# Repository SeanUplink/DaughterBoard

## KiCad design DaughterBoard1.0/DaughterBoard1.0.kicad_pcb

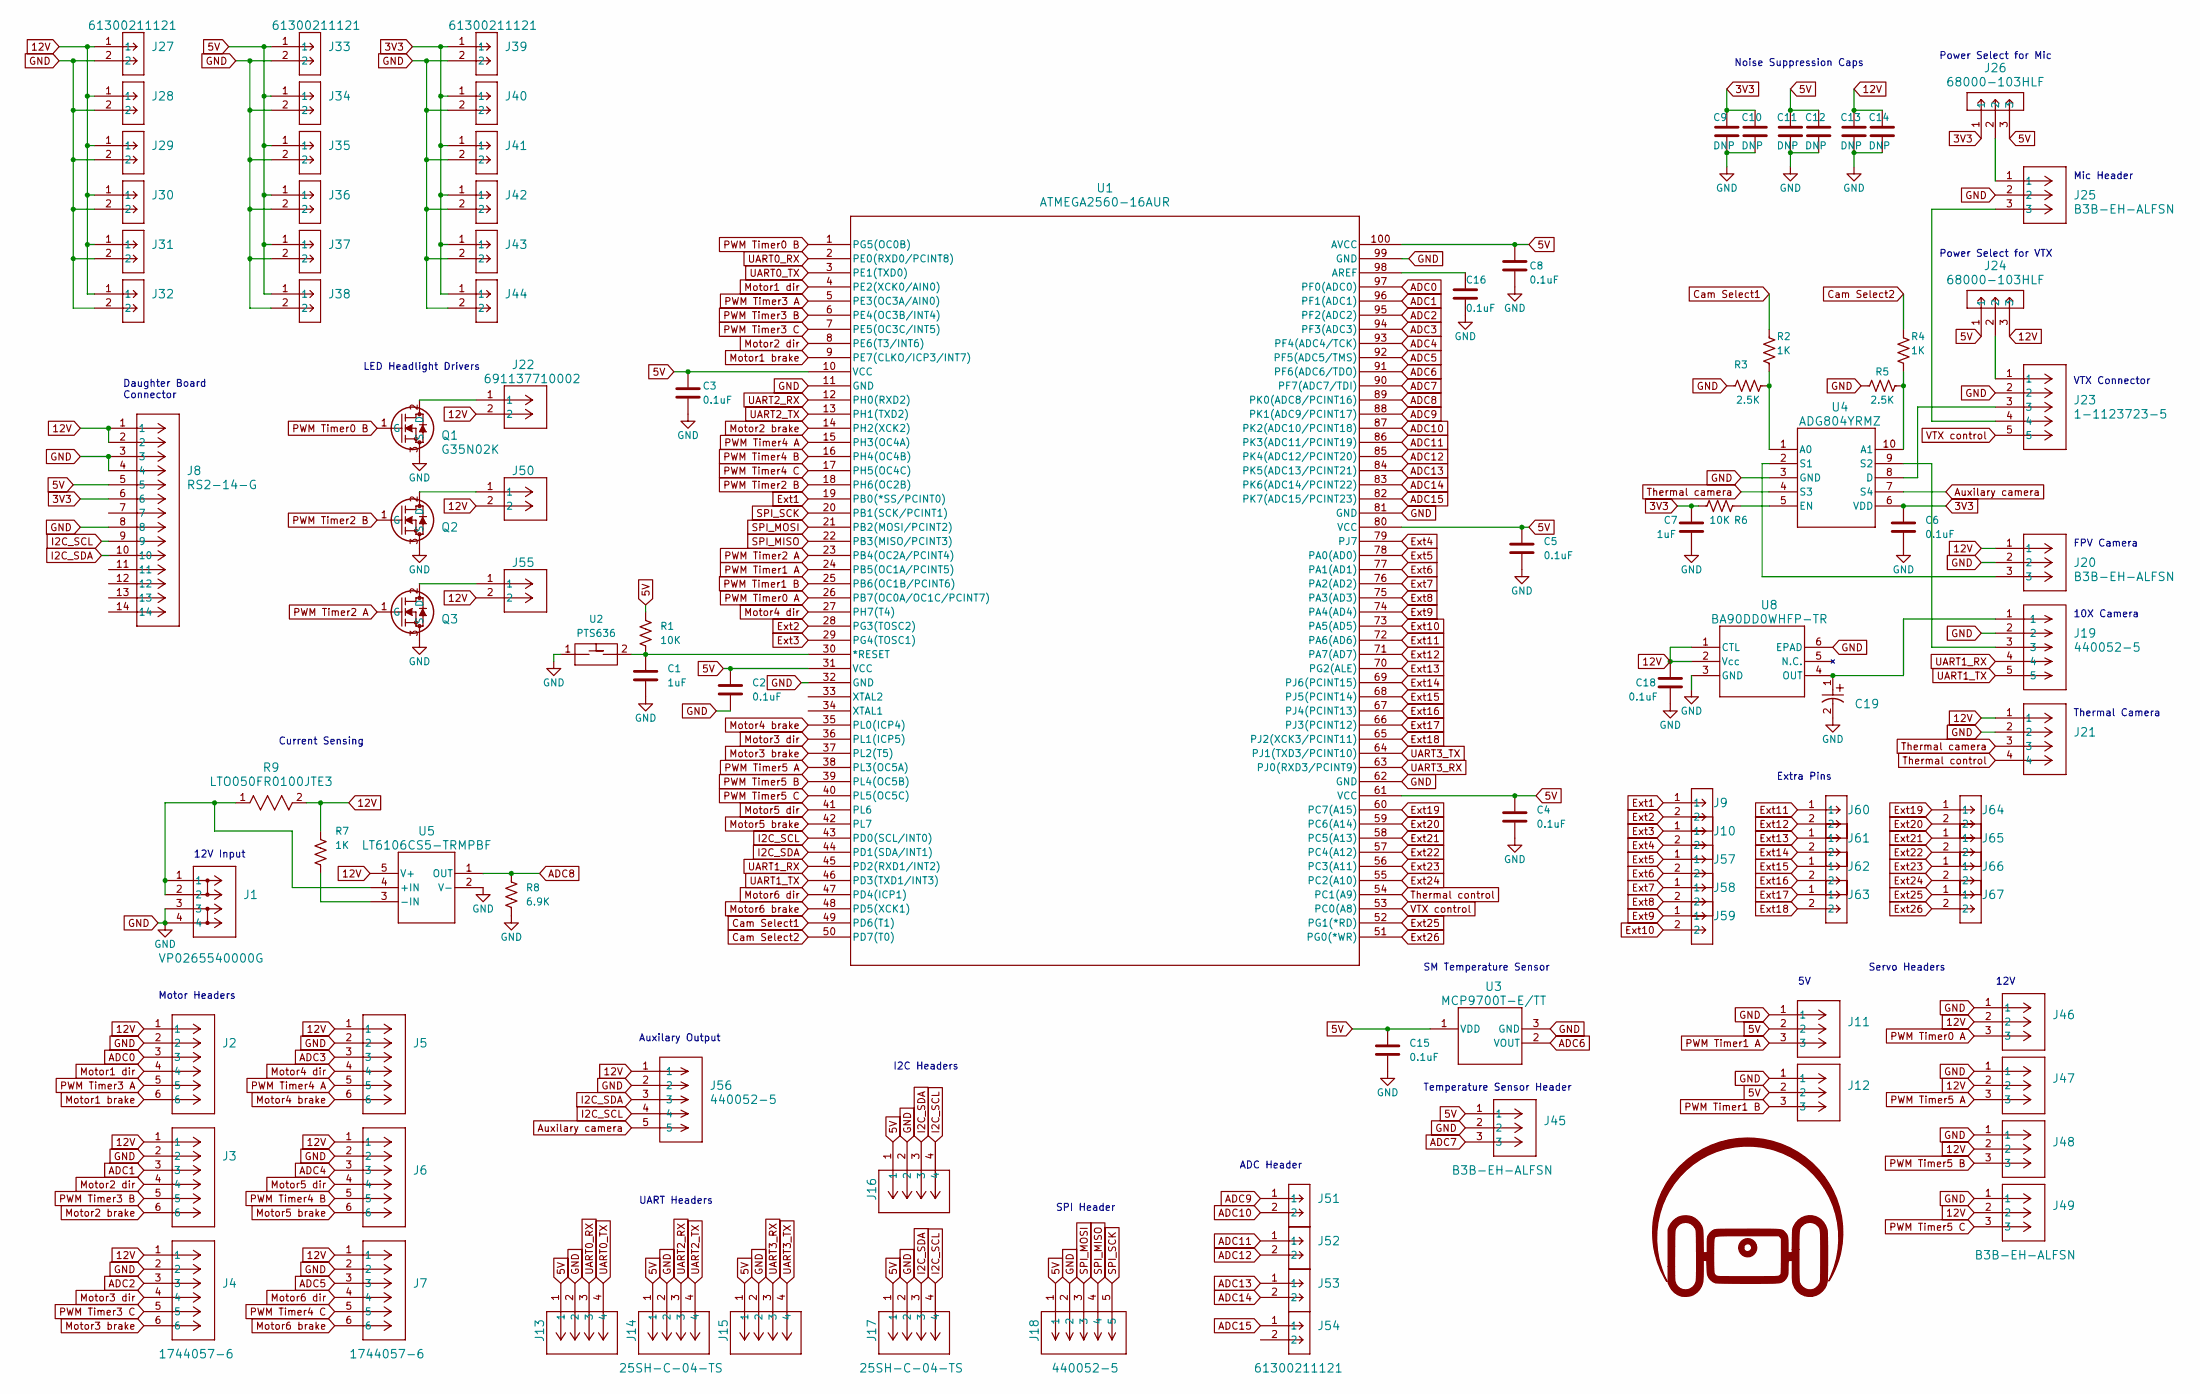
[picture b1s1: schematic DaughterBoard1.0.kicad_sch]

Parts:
C1, C7: 1uF; C_0603_1608Metric
C2, C3, C4, C5, C6, C8, C15, C16: 0.1uF; C_0603_1608Metric
C9, C10, C11, C12, C13, C14: DNP; C_0603_1608Metric
C18: 0.1uF; C_0805_2012Metric_Pad1.18x1.45mm_HandSolder
C19: TAJC226M016RNJ; TAJC_AVX
G1: LOGO; logo
J1: VP0265540000G; CONN_VP0265x4xxxxG_AMP
J2, J3, J4, J5, J6, J7: 1744057-6; conn6_1744057-6_TEC
J8: RS2-14-G; CONN_RS2-14-G_ADM
J9, J10, J27, J28, J29, J30, J31, J32, J33, J34, J35, J36, J37, J38, J39, J40, J41, J42, J43, J44, J51, J52, J53, J54, J57, J58, J59, J60, J61, J62, J63, J64, J65, J66, J67: 61300211121; CONN_61300211121_WRE
J11, J12, J20, J25, J45, J46, J47, J48, J49: B3B-EH-ALFSN; CONN3_B3B-EH-ALFSN_JST
J13, J14, J15, J16, J17, J21: 25SH-C-04-TS; CONN_B4B-EH-A_JST
J18: 440052-5; TE_440052-5; PARTREV R
J19, J56: 440052-5; conn5_1-1123723-5_TEC; PARTREV R
J22, J50, J55: 691137710002; CONN2_710002_WRE
J23: 1-1123723-5; conn5_1-1123723-5_TEC
J24, J26: 68000-103HLF; CONN_68000-103HLF_AMP
Q1, Q2, Q3: G35N02K; QNMOS1G2D3S_TO252DPAK_DIO
R1, R6: 10K; R_0603_1608Metric
R2, R4, R7: 1K; R_0603_1608Metric
R3, R5: 2.5K; R_0603_1608Metric
R8: 6.9K; R_0603_1608Metric
R9: LTO050FR0100JTE3; TO220_LTO_VIS
U1: ATMEGA2560-16AUR; TQFP100_100A_ATM
U2: PTS636
U3: MCP9700T-E/TT; SOT-23_MC_MCH
U4: ADG804YRMZ; RM_10_ADI
U5: LT6106CS5-TRMPBF; TSOT-23-5_S5_ADI
U8: BA90DD0WHFP-TR; HRP5_ROM

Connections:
3V3: C6.1, C7.1, C9.1, C10.1, J8.6, J26.1, J39.1, J40.1, J41.1, J42.1, J43.1, J44.1, R6.1, U4.6 (VDD)
5V: C2.1, C3.1, C4.1, C5.1, C8.1, C11.1, C12.1, C15.1, J8.5, J11.2, J12.2, J13.1, J14.1, J15.1, J16.1, J17.1, J18.1, J24.1, J26.3, J33.1, J34.1, J35.1, J36.1, J37.1, J38.1, J45.1, R1.1, U1.10 (VCC), U1.31 (VCC), U1.61 (VCC), U1.80 (VCC), U1.100 (AVCC), U3.1 (VDD)
12V: C13.1, C14.1, C18.1, J2.1, J3.1, J4.1, J5.1, J6.1, J7.1, J8.1, J8.2, J20.1, J21.1, J22.2, J24.3, J27.1, J28.1, J29.1, J30.1, J31.1, J32.1, J46.2, J47.2, J48.2, J49.2, J50.2, J55.2, J56.1, R7.1, R9.2, U5.5 (V+), U8.1 (CTL), U8.2 (Vcc)
ADC0: J2.3, U1.97 (PF0(ADC0))
ADC1: J3.3, U1.96 (PF1(ADC1))
ADC2: J4.3, U1.95 (PF2(ADC2))
ADC3: J5.3, U1.94 (PF3(ADC3))
ADC4: J6.3, U1.93 (PF4(ADC4/TCK))
ADC5: J7.3, U1.92 (PF5(ADC5/TMS))
ADC6: U1.91 (PF6(ADC6/TDO)), U3.2 (VOUT)
ADC7: J45.3, U1.90 (PF7(ADC7/TDI))
ADC8: R8.1, U1.89 (PK0(ADC8/PCINT16)), U5.1 (OUT)
ADC9: J51.1, U1.88 (PK1(ADC9/PCINT17))
ADC10: J51.2, U1.87 (PK2(ADC10/PCINT18))
ADC11: J52.1, U1.86 (PK3(ADC11/PCINT19))
ADC12: J52.2, U1.85 (PK4(ADC12/PCINT20))
ADC13: J53.1, U1.84 (PK5(ADC13/PCINT21))
ADC14: J53.2, U1.83 (PK6(ADC14/PCINT22))
ADC15: J54.1, U1.82 (PK7(ADC15/PCINT23))
Auxilary camera: J56.5, U4.7 (S4)
Cam Select1: R2.1, U1.49 (PD6(T1))
Cam Select2: R4.1, U1.50 (PD7(T0))
Ext1: J9.1, U1.19 (PB0(*SS/PCINT0))
Ext2: J9.2, U1.28 (PG3(TOSC2))
Ext3: J10.1, U1.29 (PG4(TOSC1))
Ext4: J10.2, U1.79 (PJ7)
Ext5: J57.1, U1.78 (PA0(AD0))
Ext6: J57.2, U1.77 (PA1(AD1))
Ext7: J58.1, U1.76 (PA2(AD2))
Ext8: J58.2, U1.75 (PA3(AD3))
Ext9: J59.1, U1.74 (PA4(AD4))
Ext10: J59.2, U1.73 (PA5(AD5))
Ext11: J60.1, U1.72 (PA6(AD6))
Ext12: J60.2, U1.71 (PA7(AD7))
Ext13: J61.1, U1.70 (PG2(ALE))
Ext14: J61.2, U1.69 (PJ6(PCINT15))
Ext15: J62.1, U1.68 (PJ5(PCINT14))
Ext16: J62.2, U1.67 (PJ4(PCINT13))
Ext17: J63.1, U1.66 (PJ3(PCINT12))
Ext18: J63.2, U1.65 (PJ2(XCK3/PCINT11))
Ext19: J64.1, U1.60 (PC7(A15))
Ext20: J64.2, U1.59 (PC6(A14))
Ext21: J65.1, U1.58 (PC5(A13))
Ext22: J65.2, U1.57 (PC4(A12))
Ext23: J66.1, U1.56 (PC3(A11))
Ext24: J66.2, U1.55 (PC2(A10))
Ext25: J67.1, U1.52 (PG1(*RD))
Ext26: J67.2, U1.51 (PG0(*WR))
GND: C1.2, C2.2, C3.2, C4.2, C5.2, C6.2, C7.2, C8.2, C9.2, C10.2, C11.2, C12.2, C13.2, C14.2, C15.2, C16.2, C18.2, C19.2, J1.3, J1.4, J2.2, J3.2, J4.2, J5.2, J6.2, J7.2, J8.3, J8.4, J8.8, J11.1, J12.1, J13.2, J14.2, J15.2, J16.2, J17.2, J18.2, J19.2, J20.2, J21.2, J23.2, J25.2, J27.2, J28.2, J29.2, J30.2, J31.2, J32.2, J33.2, J34.2, J35.2, J36.2, J37.2, J38.2, J39.2, J40.2, J41.2, J42.2, J43.2, J44.2, J45.2, J46.1, J47.1, J48.1, J49.1, J56.2, Q1.3 (S), Q2.3 (S), Q3.3 (S), R3.1, R5.1, R8.2, U1.11 (GND), U1.32 (GND), U1.62 (GND), U1.81 (GND), U1.99 (GND), U2.1, U3.3 (GND), U4.3 (GND), U5.2 (V-), U8.3 (GND), U8.6 (EPAD); also elsewhere on the board
I2C_SCL: J8.9, J16.4, J17.4, J56.4, U1.43 (PD0(SCL/INT0))
I2C_SDA: J8.10, J16.3, J17.3, J56.3, U1.44 (PD1(SDA/INT1))
Motor1 brake: J2.6, U1.9 (PE7(CLKO/ICP3/INT7))
Motor1 dir: J2.4, U1.4 (PE2(XCK0/AIN0))
Motor2 brake: J3.6, U1.14 (PH2(XCK2))
Motor2 dir: J3.4, U1.8 (PE6(T3/INT6))
Motor3 brake: J4.6, U1.37 (PL2(T5))
Motor3 dir: J4.4, U1.36 (PL1(ICP5))
Motor4 brake: J5.6, U1.35 (PL0(ICP4))
Motor4 dir: J5.4, U1.27 (PH7(T4))
Motor5 brake: J6.6, U1.42 (PL7)
Motor5 dir: J6.4, U1.41 (PL6)
Motor6 brake: J7.6, U1.48 (PD5(XCK1))
Motor6 dir: J7.4, U1.47 (PD4(ICP1))
unnamed: J23.1, J24.2
unnamed: J23.4, J25.3
unnamed: J25.1, J26.2
unnamed: J22.1, Q1.2 (D)
unnamed: J50.1, Q2.2 (D)
unnamed: J55.1, Q3.2 (D)
unnamed: C1.1, R1.2, U1.30 (*RESET), U2.2
unnamed: C16.1, U1.98 (AREF)
unnamed: R2.2, R3.2, U4.1 (A0)
unnamed: R4.2, R5.2, U4.10 (A1)
unnamed: J23.3, U4.8 (D)
unnamed: R6.2, U4.5 (EN)
unnamed: J20.3, U4.2 (S1)
unnamed: J19.3, U4.9 (S2)
unnamed: J1.1, J1.2, R9.1, U5.4 (+IN)
unnamed: R7.2, U5.3 (-IN)
unnamed: C19.1, J19.1, U8.4 (OUT)
PWM Timer0 A: J46.3, U1.26 (PB7(OC0A/OC1C/PCINT7))
PWM Timer0 B: Q1.1 (G), U1.1 (PG5(OC0B))
PWM Timer1 A: J11.3, U1.24 (PB5(OC1A/PCINT5))
PWM Timer1 B: J12.3, U1.25 (PB6(OC1B/PCINT6))
PWM Timer2 A: Q3.1 (G), U1.23 (PB4(OC2A/PCINT4))
PWM Timer2 B: Q2.1 (G), U1.18 (PH6(OC2B))
PWM Timer3 A: J2.5, U1.5 (PE3(OC3A/AIN0))
PWM Timer3 B: J3.5, U1.6 (PE4(OC3B/INT4))
PWM Timer3 C: J4.5, U1.7 (PE5(OC3C/INT5))
PWM Timer4 A: J5.5, U1.15 (PH3(OC4A))
PWM Timer4 B: J6.5, U1.16 (PH4(OC4B))
PWM Timer4 C: J7.5, U1.17 (PH5(OC4C))
PWM Timer5 A: J47.3, U1.38 (PL3(OC5A))
PWM Timer5 B: J48.3, U1.39 (PL4(OC5B))
PWM Timer5 C: J49.3, U1.40 (PL5(OC5C))
SPI_MISO: J18.4, U1.22 (PB3(MISO/PCINT3))
SPI_MOSI: J18.3, U1.21 (PB2(MOSI/PCINT2))
SPI_SCK: J18.5, U1.20 (PB1(SCK/PCINT1))
Thermal camera: J21.3, U4.4 (S3)
Thermal control: J21.4, U1.54 (PC1(A9))
UART0_RX: J13.3, U1.2 (PE0(RXD0/PCINT8))
UART0_TX: J13.4, U1.3 (PE1(TXD0))
UART1_RX: J19.4, U1.45 (PD2(RXD1/INT2))
UART1_TX: J19.5, U1.46 (PD3(TXD1/INT3))
UART2_RX: J14.3, U1.12 (PH0(RXD2))
UART2_TX: J14.4, U1.13 (PH1(TXD2))
UART3_RX: J15.3, U1.63 (PJ0(RXD3/PCINT9))
UART3_TX: J15.4, U1.64 (PJ1(TXD3/PCINT10))
VTX control: J23.5, U1.53 (PC0(A8))

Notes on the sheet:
SPI Header
FPV Camera
Mic Header
12V
Noise Suppression Caps
I2C Headers
Daughter Board Connector
Current Sensing
Power Select for Mic
Power Select for VTX
Temperature Sensor Header
SM Temperature Sensor
10X Camera
ADC Header
UART Headers
LED Headlight Drivers
Motor Headers
VTX Connector
Extra Pins
12V Input
Servo Headers
Auxilary Output
Thermal Camera

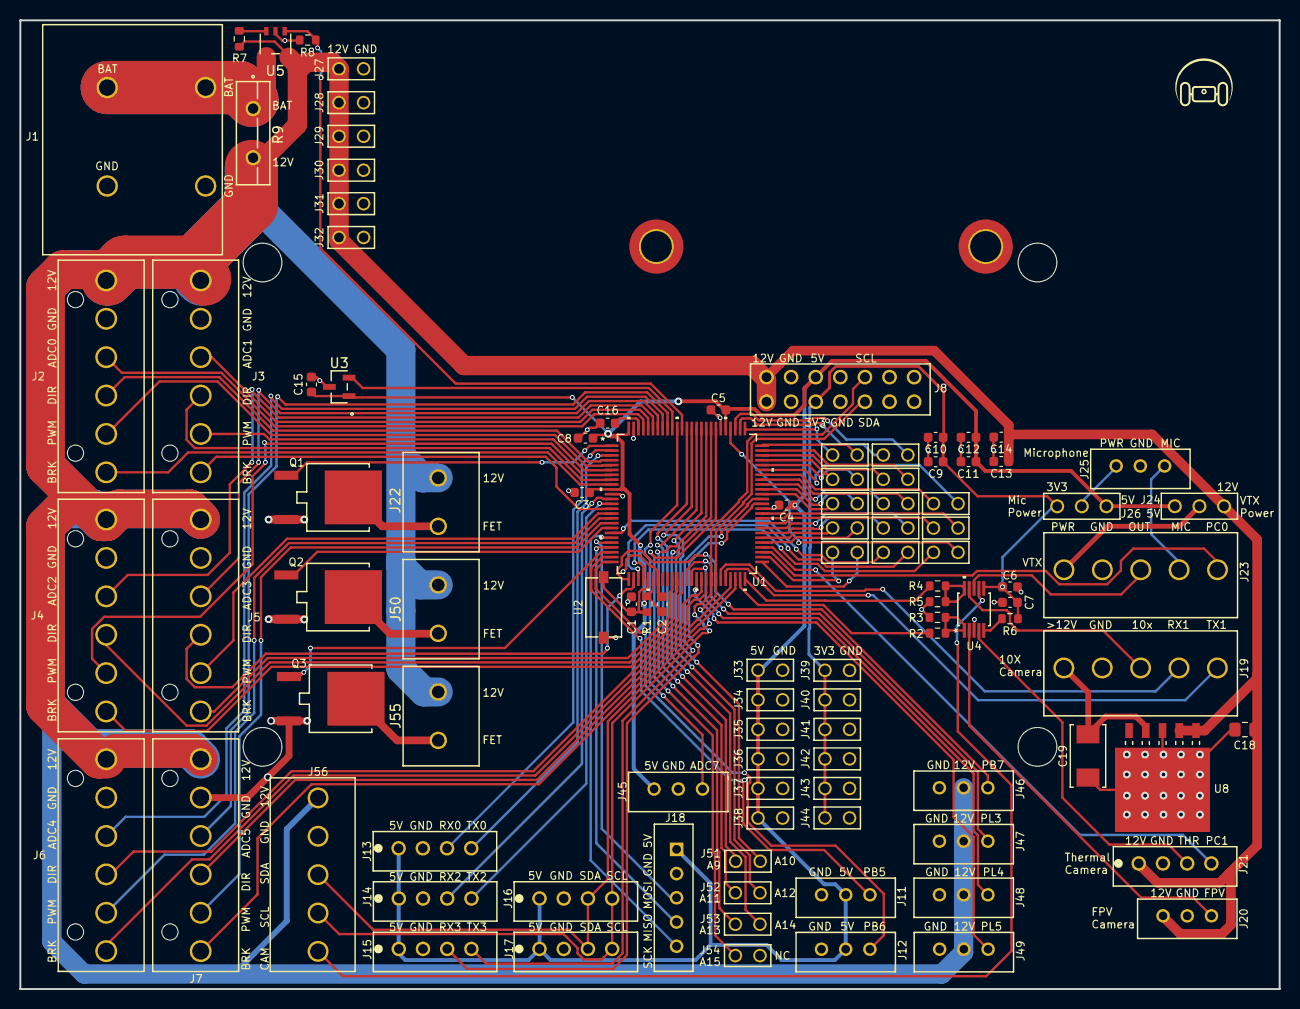
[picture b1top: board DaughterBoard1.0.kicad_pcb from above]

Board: 2 copper layers, 130.0 x 100.0 mm, 106 parts (0 on the bottom side), 109 nets.

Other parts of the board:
H1, H2: MountingHole_Pad; MountingHole_3.2mm_M3_DIN965_Pad_TopBottom

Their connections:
GND: H1.1, H2.1; also elsewhere on the board

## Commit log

2024-06-24 Updated version, basically complete. Will keep better updates moving forward
